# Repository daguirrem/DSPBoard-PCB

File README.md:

# DSPBoard PCB

This repository have PCB files from DSPBoard project, this requieres KiCAD 7.0+, includes a .zip with gerbers to fabrication.

# License
  _DSPBoard PCB_ is licensed by MIT License, more information on [LICENSE.md](LICENSE.md)

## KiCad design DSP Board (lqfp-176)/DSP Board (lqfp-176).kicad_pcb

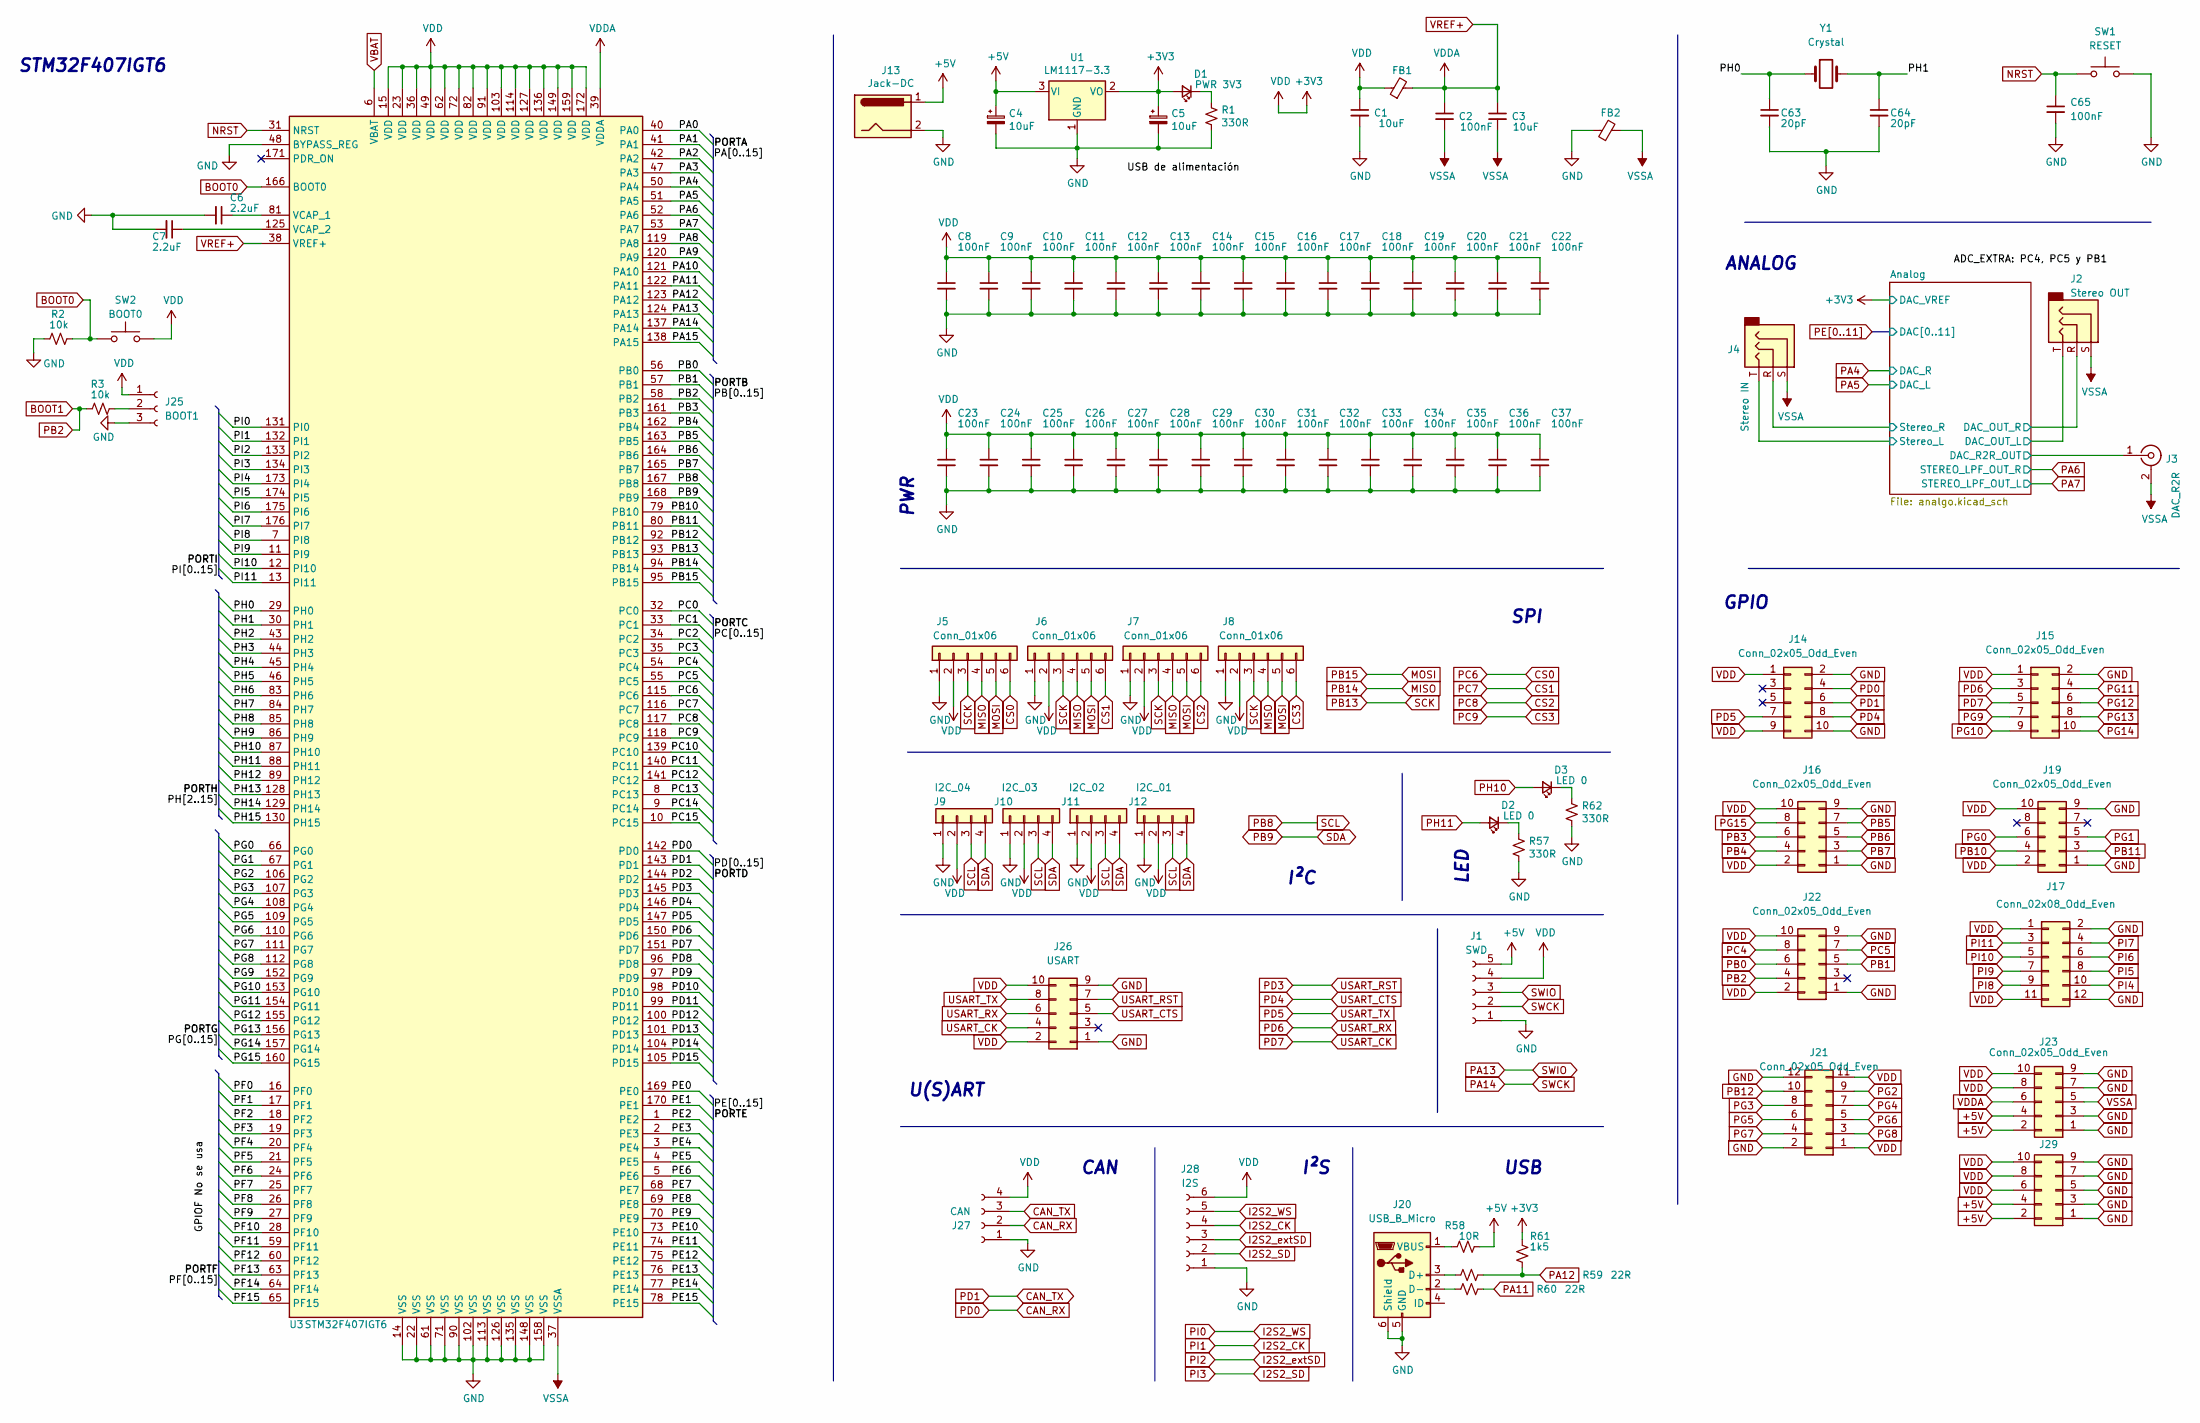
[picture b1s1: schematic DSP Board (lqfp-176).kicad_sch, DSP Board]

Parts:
C1, C3: 10uF; C_0603_1608Metric
C2, C8, C9, C10, C11, C12, C13, C14, C15, C16, C17, C18, C19, C20, C21, C22, C23, C24, C25, C26, C27, C28, C29, C30, C31, C32, C33, C34, C35, C36, C37, C65: 100nF; C_0402_1005Metric
C4, C5: 10uF; CP_Radial_D5.0mm_P2.00mm
C6, C7: 2.2uF; C_0603_1608Metric
C63, C64: 20pF; C_0402_1005Metric
D1: PWR 3V3; LED_D1.8mm_W3.3mm_H2.4mm
D2, D3: LED 0; LED_D1.8mm_W3.3mm_H2.4mm
FB1, FB2: FerriteBead_Small; LairdTech_28C0236-0JW-10
J1: SWD; PinHeader_1x05_P2.54mm_Horizontal
J2: Stereo OUT; Jack_3.5mm_Ledino_KB3SPRS_Horizontal
J3: DAC_R2R; rca_black
J4: Stereo IN; Jack_3.5mm_Ledino_KB3SPRS_Horizontal
J5, J6, J7, J8: Conn_01x06; PinSocket_1x06_P2.54mm_Vertical
J9: I2C_04; PinSocket_1x04_P2.54mm_Vertical
J10: I2C_03; PinSocket_1x04_P2.54mm_Vertical
J11: I2C_02; PinSocket_1x04_P2.54mm_Vertical
J12: I2C_01; PinSocket_1x04_P2.54mm_Vertical
J13: Jack-DC; BarrelJack_Horizontal
J14, J15, J16, J19, J22, J23, J29: Conn_02x05_Odd_Even; PinSocket_2x05_P2.54mm_Vertical
J17: Conn_02x08_Odd_Even; PinSocket_2x06_P2.54mm_Vertical
J20: USB_B_Micro; USB_Micro-B_Molex_47346-0001
J21: Conn_02x05_Odd_Even; PinSocket_2x06_P2.54mm_Vertical
J25: BOOT1; PinHeader_1x03_P2.54mm_Vertical
J26: USART; PinSocket_2x05_P2.54mm_Vertical
J27: CAN; PinSocket_1x04_P2.54mm_Vertical
J28: I2S; PinSocket_1x06_P2.54mm_Vertical
R1, R57, R62: 330R; R_0603_1608Metric_Pad0.98x0.95mm_HandSolder
R2, R3: 10k; R_0603_1608Metric_Pad0.98x0.95mm_HandSolder
R58: 10R; R_0603_1608Metric_Pad0.98x0.95mm_HandSolder
R59, R60: 22R; R_0603_1608Metric_Pad0.98x0.95mm_HandSolder
R61: 1k5; R_0603_1608Metric_Pad0.98x0.95mm_HandSolder
SW1: RESET; SW_PUSH_6mm
SW2: BOOT0; SW_PUSH_6mm
U1: LM1117-3.3; SOT-223-3_TabPin2
U3: STM32F407IGT6; LQFP-176_24x24mm_P0.5mm
Y1: Crystal; Crystal_HC49-4H_Vertical

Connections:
+5V: C4.1, J1.5, J13.1, J23.2, J23.4, J29.2, J29.4, R58.2, U1.3 (VI); also elsewhere on the board
/Analog/DAC_OUT_L: J2.T; also elsewhere on the board
/Analog/DAC_OUT_R: J2.R; also elsewhere on the board
/Analog/DAC_R2R_OUT: J3.1 (In); also elsewhere on the board
/Analog/Stereo_L: J4.T; also elsewhere on the board
/Analog/Stereo_R: J4.R; also elsewhere on the board
/PA0: U3.40 (PA0)
/PA1: U3.41 (PA1)
/PA2: U3.42 (PA2)
/PA3: U3.47 (PA3)
/PA8: U3.119 (PA8)
/PA9: U3.120 (PA9)
/PA10: U3.121 (PA10)
/PA15: U3.138 (PA15)
/PC0: U3.32 (PC0)
/PC1: U3.33 (PC1)
/PC2: U3.34 (PC2)
/PC3: U3.35 (PC3)
/PC10: U3.139 (PC10)
/PC11: U3.140 (PC11)
/PC12: U3.141 (PC12)
/PC13: U3.8 (PC13)
/PC14: U3.9 (PC14)
/PC15: U3.10 (PC15)
/PD2: U3.144 (PD2)
/PD8: U3.96 (PD8)
/PD9: U3.97 (PD9)
/PD10: U3.98 (PD10)
/PD11: U3.99 (PD11)
/PD12: U3.100 (PD12)
/PD13: U3.101 (PD13)
/PD14: U3.104 (PD14)
/PD15: U3.105 (PD15)
/PE0: U3.169 (PE0); also elsewhere on the board
/PE1: U3.170 (PE1); also elsewhere on the board
/PE2: U3.1 (PE2); also elsewhere on the board
/PE3: U3.2 (PE3); also elsewhere on the board
/PE4: U3.3 (PE4); also elsewhere on the board
/PE5: U3.4 (PE5); also elsewhere on the board
/PE6: U3.5 (PE6); also elsewhere on the board
/PE7: U3.68 (PE7); also elsewhere on the board
/PE8: U3.69 (PE8); also elsewhere on the board
/PE9: U3.70 (PE9); also elsewhere on the board
/PE10: U3.73 (PE10); also elsewhere on the board
/PE11: U3.74 (PE11); also elsewhere on the board
/PE12: U3.75 (PE12)
/PE13: U3.76 (PE13)
/PE14: U3.77 (PE14)
/PE15: U3.78 (PE15)
/PF0: U3.16 (PF0)
/PF1: U3.17 (PF1)
/PF2: U3.18 (PF2)
/PF3: U3.19 (PF3)
/PF4: U3.20 (PF4)
/PF5: U3.21 (PF5)
/PF6: U3.24 (PF6)
/PF7: U3.25 (PF7)
/PF8: U3.26 (PF8)
/PF9: U3.27 (PF9)
/PF10: U3.28 (PF10)
/PF11: U3.59 (PF11)
/PF12: U3.60 (PF12)
/PF13: U3.63 (PF13)
/PF14: U3.64 (PF14)
/PF15: U3.65 (PF15)
/PH0: C63.1, U3.29 (PH0), Y1.1
/PH1: C64.1, U3.30 (PH1), Y1.2
/PH2: U3.43 (PH2)
/PH3: U3.44 (PH3)
/PH4: U3.45 (PH4)
/PH5: U3.46 (PH5)
/PH6: U3.83 (PH6)
/PH7: U3.84 (PH7)
/PH8: U3.85 (PH8)
/PH9: U3.86 (PH9)
/PH12: U3.89 (PH12)
/PH13: U3.128 (PH13)
/PH14: U3.129 (PH14)
/PH15: U3.130 (PH15)
BOOT0: R2.2, SW2.1, U3.166 (BOOT0)
BOOT1: J22.4, R3.2, U3.58 (PB2)
CAN_RX: J14.4, J27.2, U3.142 (PD0)
CAN_TX: J14.6, J27.3, U3.143 (PD1)
CS0: J5.6, U3.115 (PC6)
CS1: J6.6, U3.116 (PC7)
CS2: J7.6, U3.117 (PC8)
CS3: J8.6, U3.118 (PC9)
GND: C1.2, C4.2, C5.2, C6.2, C7.2, C8.2, C9.2, C10.2, C11.2, C12.2, C13.2, C14.2, C15.2, C16.2, C17.2, C18.2, C19.2, C20.2, C21.2, C22.2, C23.2, C24.2, C25.2, C26.2, C27.2, C28.2, C29.2, C30.2, C31.2, C32.2, C33.2, C34.2, C35.2, C36.2, C37.2, C63.2, C64.2, C65.2, FB2.1, J1.1, J5.1, J6.1, J7.1, J8.1, J9.1, J10.1, J11.1, J12.1, J13.2, J14.2, J14.10, J15.2, J16.1, J16.9, J17.2, J17.12, J19.1, J19.9, J20.5 (GND), J20.6 (Shield), J21.2, J21.12, J22.1, J22.9, J23.1, J23.3, J23.7, J23.9, J25.3, J26.1, J26.9, J27.1, J28.1, J29.1, J29.3, J29.5, J29.7, J29.9, R1.2, R2.1, R57.2, R62.2, SW1.2, U1.1 (GND), U3.14 (VSS), U3.22 (VSS), U3.48 (BYPASS_REG), U3.61 (VSS), U3.71 (VSS), U3.90 (VSS), U3.102 (VSS), U3.113 (VSS), U3.126 (VSS), U3.135 (VSS), U3.148 (VSS), U3.158 (VSS); also elsewhere on the board
I2S2_CK: J28.4, U3.132 (PI1)
I2S2_SD: J28.2, U3.134 (PI3)
I2S2_WS: J28.5, U3.131 (PI0)
I2S2_extSD: J28.3, U3.133 (PI2)
MISO: J5.4, J6.4, J7.4, J8.4, U3.94 (PB14)
MOSI: J5.5, J6.5, J7.5, J8.5, U3.95 (PB15)
NRST: C65.1, SW1.1, U3.31 (NRST)
unnamed: D1.1 (K), R1.1
unnamed: D2.1 (K), R57.1
unnamed: D3.1 (K), R62.1
unnamed: J20.3 (D+), R59.1
unnamed: J20.2 (D-), R60.1
unnamed: J20.1 (VBUS), R58.1
unnamed: J25.2, R3.1
unnamed: C6.1, U3.81 (VCAP_1)
unnamed: C7.1, U3.125 (VCAP_2)
PA4: U3.50 (PA4); also elsewhere on the board
PA5: U3.51 (PA5); also elsewhere on the board
PA6: U3.52 (PA6); also elsewhere on the board
PA7: U3.53 (PA7); also elsewhere on the board
PA11: R60.2, U3.122 (PA11)
PA12: R59.2, R61.2, U3.123 (PA12)
PA13: J1.3, U3.124 (PA13)
PA14: J1.2, U3.137 (PA14)
PB0: J22.6, U3.56 (PB0)
PB1: J22.5, U3.57 (PB1)
PB3: J16.6, U3.161 (PB3)
PB4: J16.4, U3.162 (PB4)
PB5: J16.7, U3.163 (PB5)
PB6: J16.5, U3.164 (PB6)
PB7: J16.3, U3.165 (PB7)
PB8: J9.3, J10.3, J11.3, J12.3, U3.167 (PB8)
PB9: J9.4, J10.4, J11.4, J12.4, U3.168 (PB9)
PB10: J19.4, U3.79 (PB10)
PB11: J19.3, U3.80 (PB11)
PB12: J21.10, U3.92 (PB12)
PB13: J5.3, J6.3, J7.3, J8.3, U3.93 (PB13)
PC4: J22.8, U3.54 (PC4)
PC5: J22.7, U3.55 (PC5)
PD3: J26.7, U3.145 (PD3)
PD4: J14.8, J26.5, U3.146 (PD4)
PD5: J14.7, J26.8, U3.147 (PD5)
PD6: J15.3, J26.6, U3.150 (PD6)
PD7: J15.5, J26.4, U3.151 (PD7)
PG0: J19.6, U3.66 (PG0)
PG1: J19.5, U3.67 (PG1)
PG2: J21.9, U3.106 (PG2)
PG3: J21.8, U3.107 (PG3)
PG4: J21.7, U3.108 (PG4)
PG5: J21.6, U3.109 (PG5)
PG6: J21.5, U3.110 (PG6)
PG7: J21.4, U3.111 (PG7)
PG8: J21.3, U3.112 (PG8)
PG9: J15.7, U3.152 (PG9)
PG10: J15.9, U3.153 (PG10)
PG11: J15.4, U3.154 (PG11)
PG12: J15.6, U3.155 (PG12)
PG13: J15.8, U3.156 (PG13)
PG14: J15.10, U3.157 (PG14)
PG15: J16.8, U3.160 (PG15)
PH10: D3.2 (A), U3.87 (PH10)
PH11: D2.2 (A), U3.88 (PH11)
PI4: J17.10, U3.173 (PI4)
PI5: J17.8, U3.174 (PI5)
PI6: J17.6, U3.175 (PI6)
PI7: J17.4, U3.176 (PI7)
PI8: J17.9, U3.7 (PI8)
PI9: J17.7, U3.11 (PI9)
PI10: J17.5, U3.12 (PI10)
PI11: J17.3, U3.13 (PI11)
VBAT: U3.6 (VBAT)
VDD: C1.1, C5.1, C8.1, C9.1, C10.1, C11.1, C12.1, C13.1, C14.1, C15.1, C16.1, C17.1, C18.1, C19.1, C20.1, C21.1, C22.1, C23.1, C24.1, C25.1, C26.1, C27.1, C28.1, C29.1, C30.1, C31.1, C32.1, C33.1, C34.1, C35.1, C36.1, C37.1, D1.2 (A), FB1.1, J1.4, J5.2, J6.2, J7.2, J8.2, J9.2, J10.2, J11.2, J12.2, J14.1, J14.9, J15.1, J16.2, J16.10, J17.1, J17.11, J19.2, J19.10, J21.1, J21.11, J22.2, J22.10, J23.8, J23.10, J25.1, J26.2, J26.10, J27.4, J28.6, J29.6, J29.8, J29.10, R61.1, SW2.2, U1.2 (VO), U3.15 (VDD), U3.23 (VDD), U3.36 (VDD), U3.49 (VDD), U3.62 (VDD), U3.72 (VDD), U3.82 (VDD), U3.91 (VDD), U3.103 (VDD), U3.114 (VDD), U3.127 (VDD), U3.136 (VDD), U3.149 (VDD), U3.159 (VDD), U3.172 (VDD)
VDDA: C2.1, C3.1, FB1.2, J23.6, U3.38 (VREF+), U3.39 (VDDA); also elsewhere on the board
VSSA: C2.2, C3.2, FB2.2, J2.S, J3.2 (Ext), J4.S, J23.5, U3.37 (VSSA); also elsewhere on the board

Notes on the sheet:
I²S
SPI
LED
PWR
USB
I²C
ANALOG
CAN
U(S)ART
GPIO
STM32F407IGT6

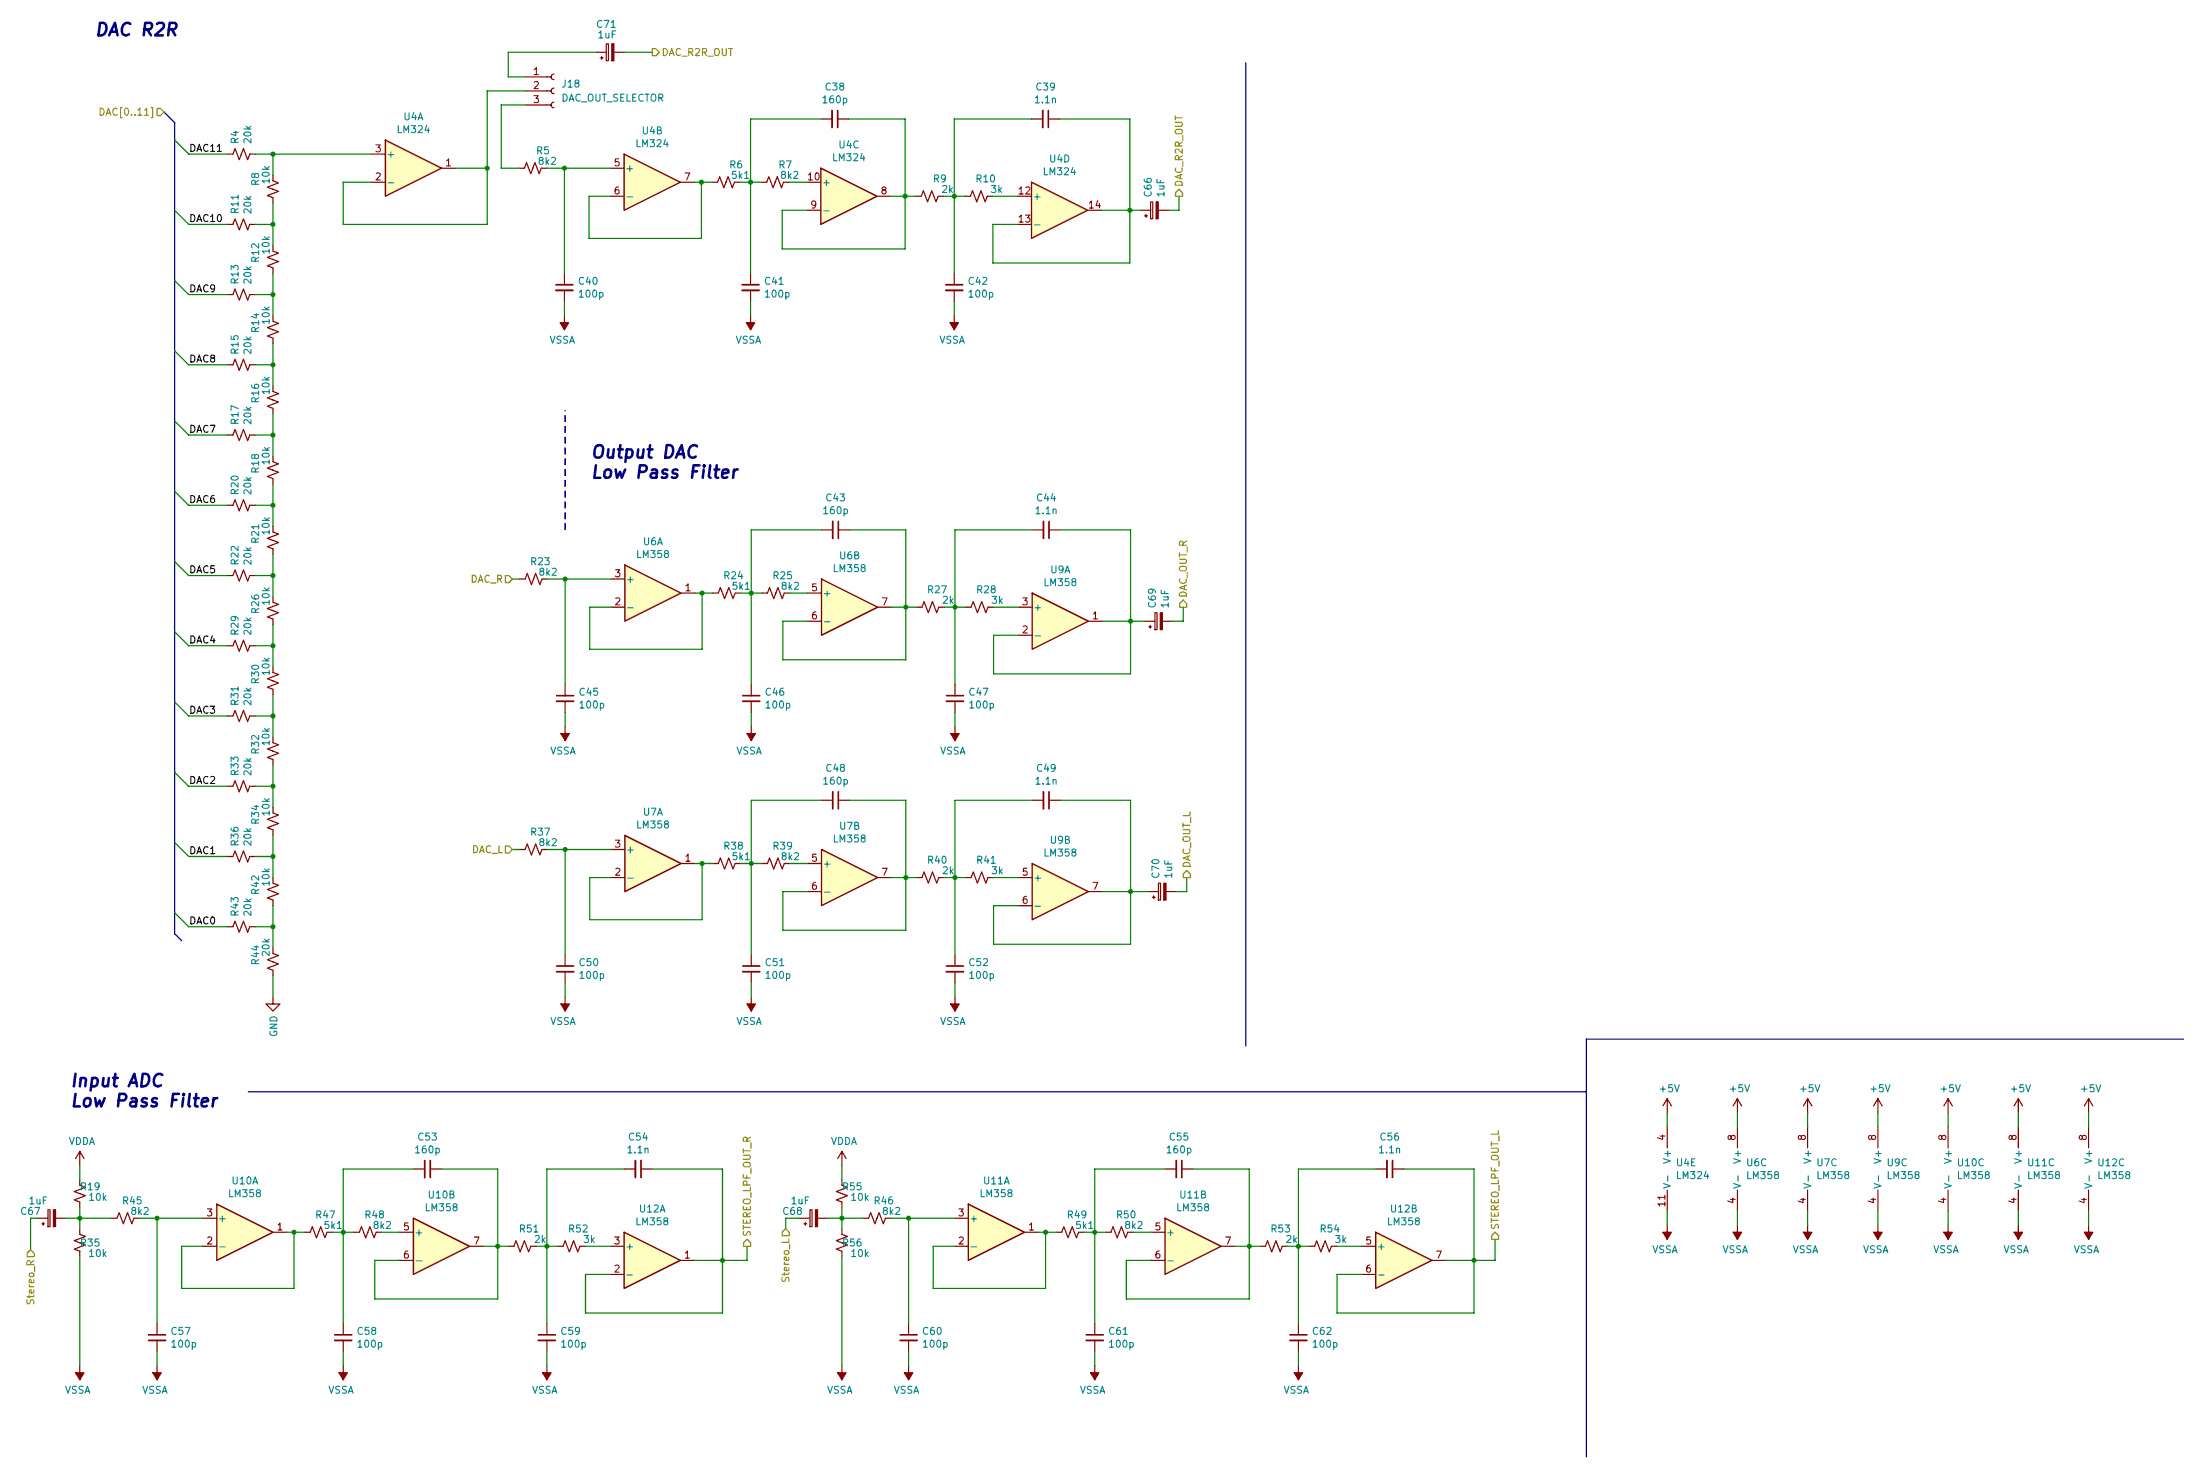
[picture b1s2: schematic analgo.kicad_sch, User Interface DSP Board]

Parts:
C38, C43, C48, C53, C55: 160p; C_0603_1608Metric
C39, C44, C49, C54, C56: 1.1n; C_0603_1608Metric
C40, C41, C42, C45, C46, C47, C50, C51, C52, C57, C58, C59, C60, C61, C62: 100p; C_0603_1608Metric
C66, C67, C68, C69, C70, C71: 1uF; CP_Radial_D4.0mm_P1.50mm
J18: DAC_OUT_SELECTOR; PinHeader_1x03_P2.54mm_Vertical
R4, R11, R13, R15, R17, R20, R22, R29, R31, R33, R36, R43, R44: 20k; R_0603_1608Metric_Pad0.98x0.95mm_HandSolder
R5, R7, R23, R25, R37, R39, R45, R46, R48, R50: 8k2; R_0603_1608Metric_Pad0.98x0.95mm_HandSolder
R6, R24, R38, R47, R49: 5k1; R_0603_1608Metric_Pad0.98x0.95mm_HandSolder
R8, R12, R14, R16, R18, R19, R21, R26, R30, R32, R34, R35, R42, R55, R56: 10k; R_0603_1608Metric_Pad0.98x0.95mm_HandSolder
R9, R27, R40, R51, R53: 2k; R_0603_1608Metric_Pad0.98x0.95mm_HandSolder
R10, R28, R41, R52, R54: 3k; R_0603_1608Metric_Pad0.98x0.95mm_HandSolder
U4: LM324; SOIC-14_3.9x8.7mm_P1.27mm
U6, U7, U9, U10, U11, U12: LM358; SOIC-8_3.9x4.9mm_P1.27mm

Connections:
+5V: U4.4 (V+), U6.8 (V+), U7.8 (V+), U9.8 (V+), U10.8 (V+), U11.8 (V+), U12.8 (V+); also elsewhere on the board
/Analog/DAC_OUT_L: C70.2; also elsewhere on the board
/Analog/DAC_OUT_R: C69.2; also elsewhere on the board
/Analog/DAC_R2R_OUT: C66.2, C71.2; also elsewhere on the board
/Analog/Stereo_L: C68.1; also elsewhere on the board
/Analog/Stereo_R: C67.1; also elsewhere on the board
/PE0: R43.1; also elsewhere on the board
/PE1: R36.1; also elsewhere on the board
/PE2: R33.1; also elsewhere on the board
/PE3: R31.1; also elsewhere on the board
/PE4: R29.1; also elsewhere on the board
/PE5: R22.1; also elsewhere on the board
/PE6: R20.1; also elsewhere on the board
/PE7: R17.1; also elsewhere on the board
/PE8: R15.1; also elsewhere on the board
/PE9: R13.1; also elsewhere on the board
/PE10: R11.1; also elsewhere on the board
/PE11: R4.1; also elsewhere on the board
GND: R44.1; also elsewhere on the board
unnamed: C38.2, C41.1, R6.2, R7.1
unnamed: C39.2, C42.1, R9.2, R10.1
unnamed: C43.2, C46.1, R24.2, R25.1
unnamed: C44.2, C47.1, R27.2, R28.1
unnamed: C48.2, C51.1, R38.2, R39.1
unnamed: C49.2, C52.1, R40.2, R41.1
unnamed: C53.2, C58.1, R47.2, R48.1
unnamed: C54.2, C59.1, R51.2, R52.1
unnamed: C55.2, C61.1, R49.2, R50.1
unnamed: C56.2, C62.1, R53.2, R54.1
unnamed: C67.2, R19.1, R35.2, R45.1
unnamed: C68.2, R46.1, R55.1, R56.2
unnamed: C71.1, J18.1
unnamed: J18.2, U4.1, U4.2 (-)
unnamed: J18.3, R5.1
unnamed: R8.1, R11.2, R12.2
unnamed: R12.1, R13.2, R14.2
unnamed: R14.1, R15.2, R16.2
unnamed: R16.1, R17.2, R18.2
unnamed: R18.1, R20.2, R21.2
unnamed: R21.1, R22.2, R26.2
unnamed: R26.1, R29.2, R30.2
unnamed: R30.1, R31.2, R32.2
unnamed: R32.1, R33.2, R34.2
unnamed: R34.1, R36.2, R42.2
unnamed: R42.1, R43.2, R44.2
unnamed: R4.2, R8.2, U4.3 (+)
unnamed: C40.1, R5.2, U4.5 (+)
unnamed: R6.1, U4.6 (-), U4.7
unnamed: R7.2, U4.10 (+)
unnamed: C38.1, R9.1, U4.8, U4.9 (-)
unnamed: R10.2, U4.12 (+)
unnamed: C39.1, C66.1, U4.13 (-), U4.14
unnamed: C45.1, R23.2, U6.3 (+)
unnamed: R24.1, U6.1, U6.2 (-)
unnamed: R25.2, U6.5 (+)
unnamed: C43.1, R27.1, U6.6 (-), U6.7
unnamed: C50.1, R37.2, U7.3 (+)
unnamed: R38.1, U7.1, U7.2 (-)
unnamed: R39.2, U7.5 (+)
unnamed: C48.1, R40.1, U7.6 (-), U7.7
unnamed: R28.2, U9.3 (+)
unnamed: C44.1, C69.1, U9.1, U9.2 (-)
unnamed: R41.2, U9.5 (+)
unnamed: C49.1, C70.1, U9.6 (-), U9.7
unnamed: C57.1, R45.2, U10.3 (+)
unnamed: R47.1, U10.1, U10.2 (-)
unnamed: R48.2, U10.5 (+)
unnamed: C53.1, R51.1, U10.6 (-), U10.7
unnamed: C60.1, R46.2, U11.3 (+)
unnamed: R49.1, U11.1, U11.2 (-)
unnamed: R50.2, U11.5 (+)
unnamed: C55.1, R53.1, U11.6 (-), U11.7
unnamed: R52.2, U12.3 (+)
unnamed: R54.2, U12.5 (+)
PA4: R23.1; also elsewhere on the board
PA5: R37.1; also elsewhere on the board
PA6: C54.1, U12.1, U12.2 (-); also elsewhere on the board
PA7: C56.1, U12.6 (-), U12.7; also elsewhere on the board
VDDA: R19.2, R55.2; also elsewhere on the board
VSSA: C40.2, C41.2, C42.2, C45.2, C46.2, C47.2, C50.2, C51.2, C52.2, C57.2, C58.2, C59.2, C60.2, C61.2, C62.2, R35.1, R56.1, U4.11 (V-), U6.4 (V-), U7.4 (V-), U9.4 (V-), U10.4 (V-), U11.4 (V-), U12.4 (V-); also elsewhere on the board

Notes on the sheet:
DAC R2R
Input ADC Low Pass Filter
Output DAC Low Pass Filter

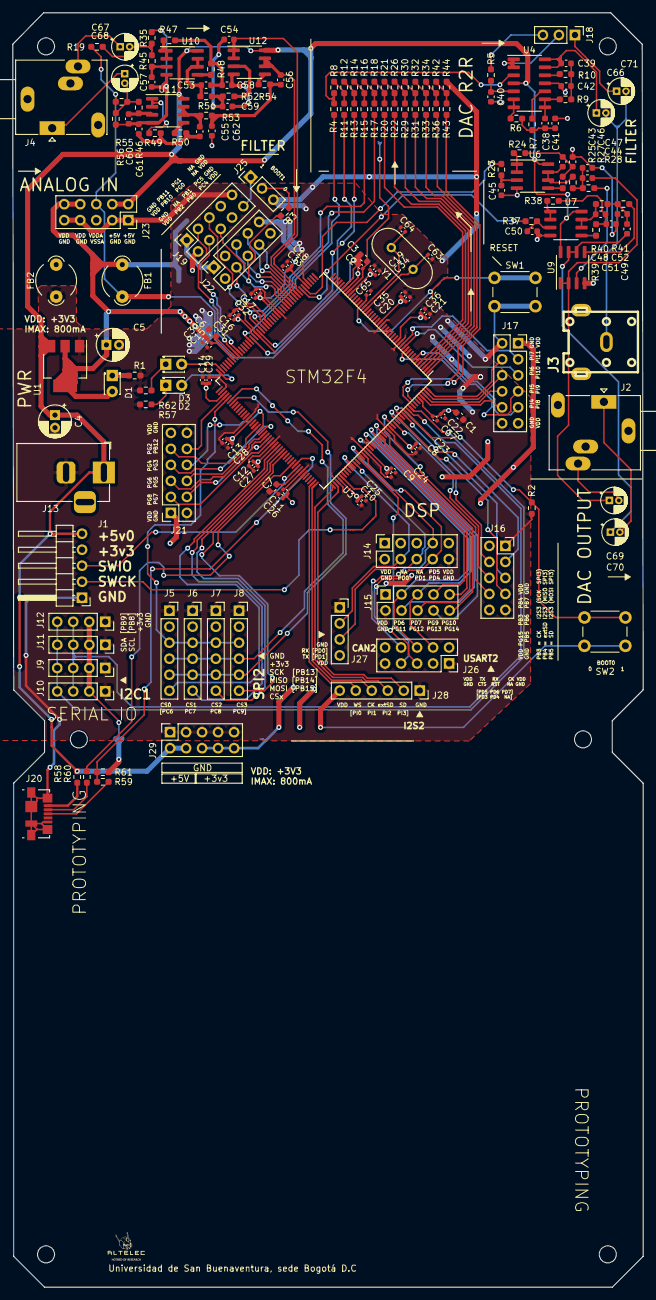
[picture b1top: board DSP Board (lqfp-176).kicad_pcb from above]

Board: 2 copper layers, 100.0 x 202.3 mm, 178 parts (0 on the bottom side), 157 nets.

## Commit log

2024-05-21 DSPBoard-PCB repo migration [REVB.1]
2024-05-21 fix minor title mistake.
